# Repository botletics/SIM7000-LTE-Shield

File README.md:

## Overview
This shield uses SIMCOM's SIM7000-series module, a low-power cellular module that supports LTE CAT-M1 and NB-IoT technology and integrated multi-GNSS (GPS, GLONASS and BeiDou/Compass, Galileo, QZSS standards) for location tracking. The shield also includes a high-accuracy I2C temperature sensor for IoT monitoring applications.

- [Buy shield on Amazon](http://a.co/d/eQ2l2TL)
- [Step-by-step wiki](https://github.com/botletics/SIM7000-LTE-Shield/wiki)
- [Arduino library with example code](https://github.com/botletics/Botletics-SIM7000) 
- [Botletics community forum](https://forum.botletics.com/) 

All PCB design files and hardware are released under the [Creative Commons Attribution Share Alike 4.0 license](https://choosealicense.com/licenses/cc-by-sa-4.0/).

All other software is released under the [GNU General Public License v3.0](https://choosealicense.com/licenses/gpl-3.0/).

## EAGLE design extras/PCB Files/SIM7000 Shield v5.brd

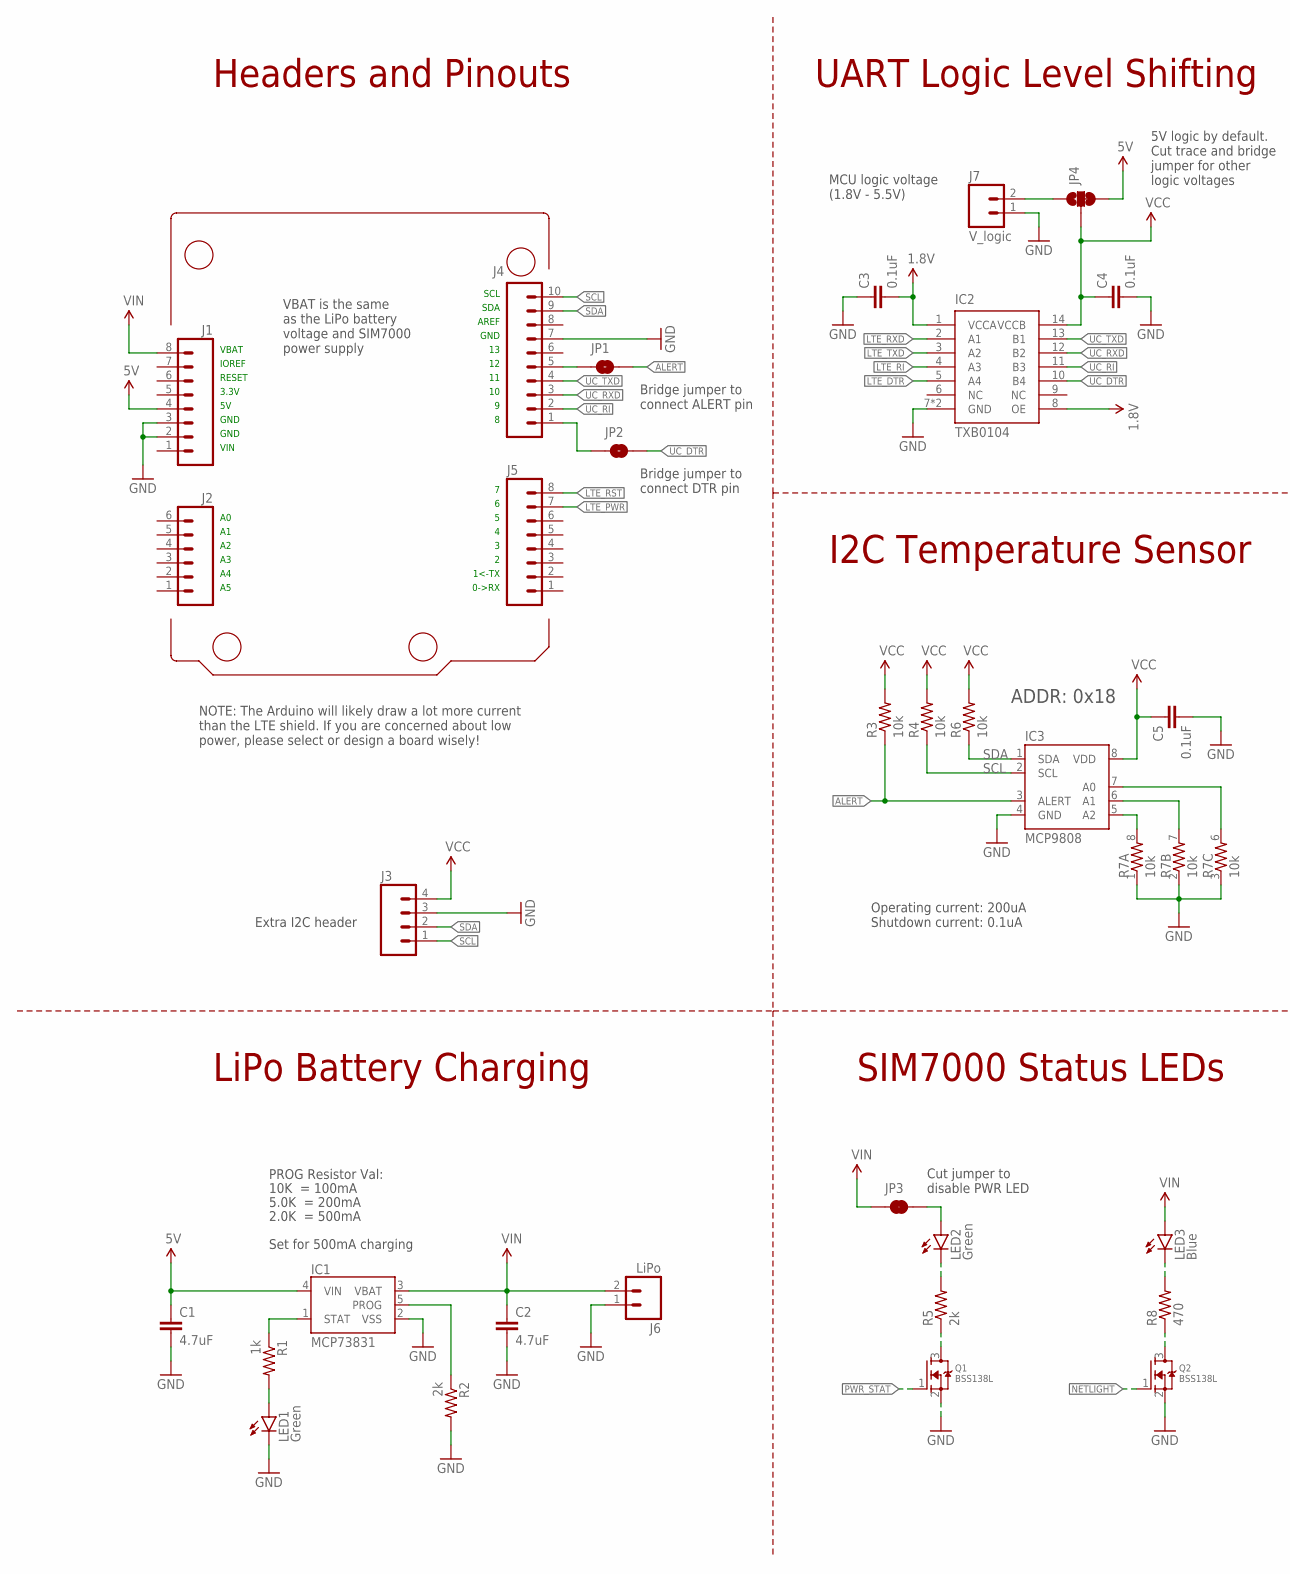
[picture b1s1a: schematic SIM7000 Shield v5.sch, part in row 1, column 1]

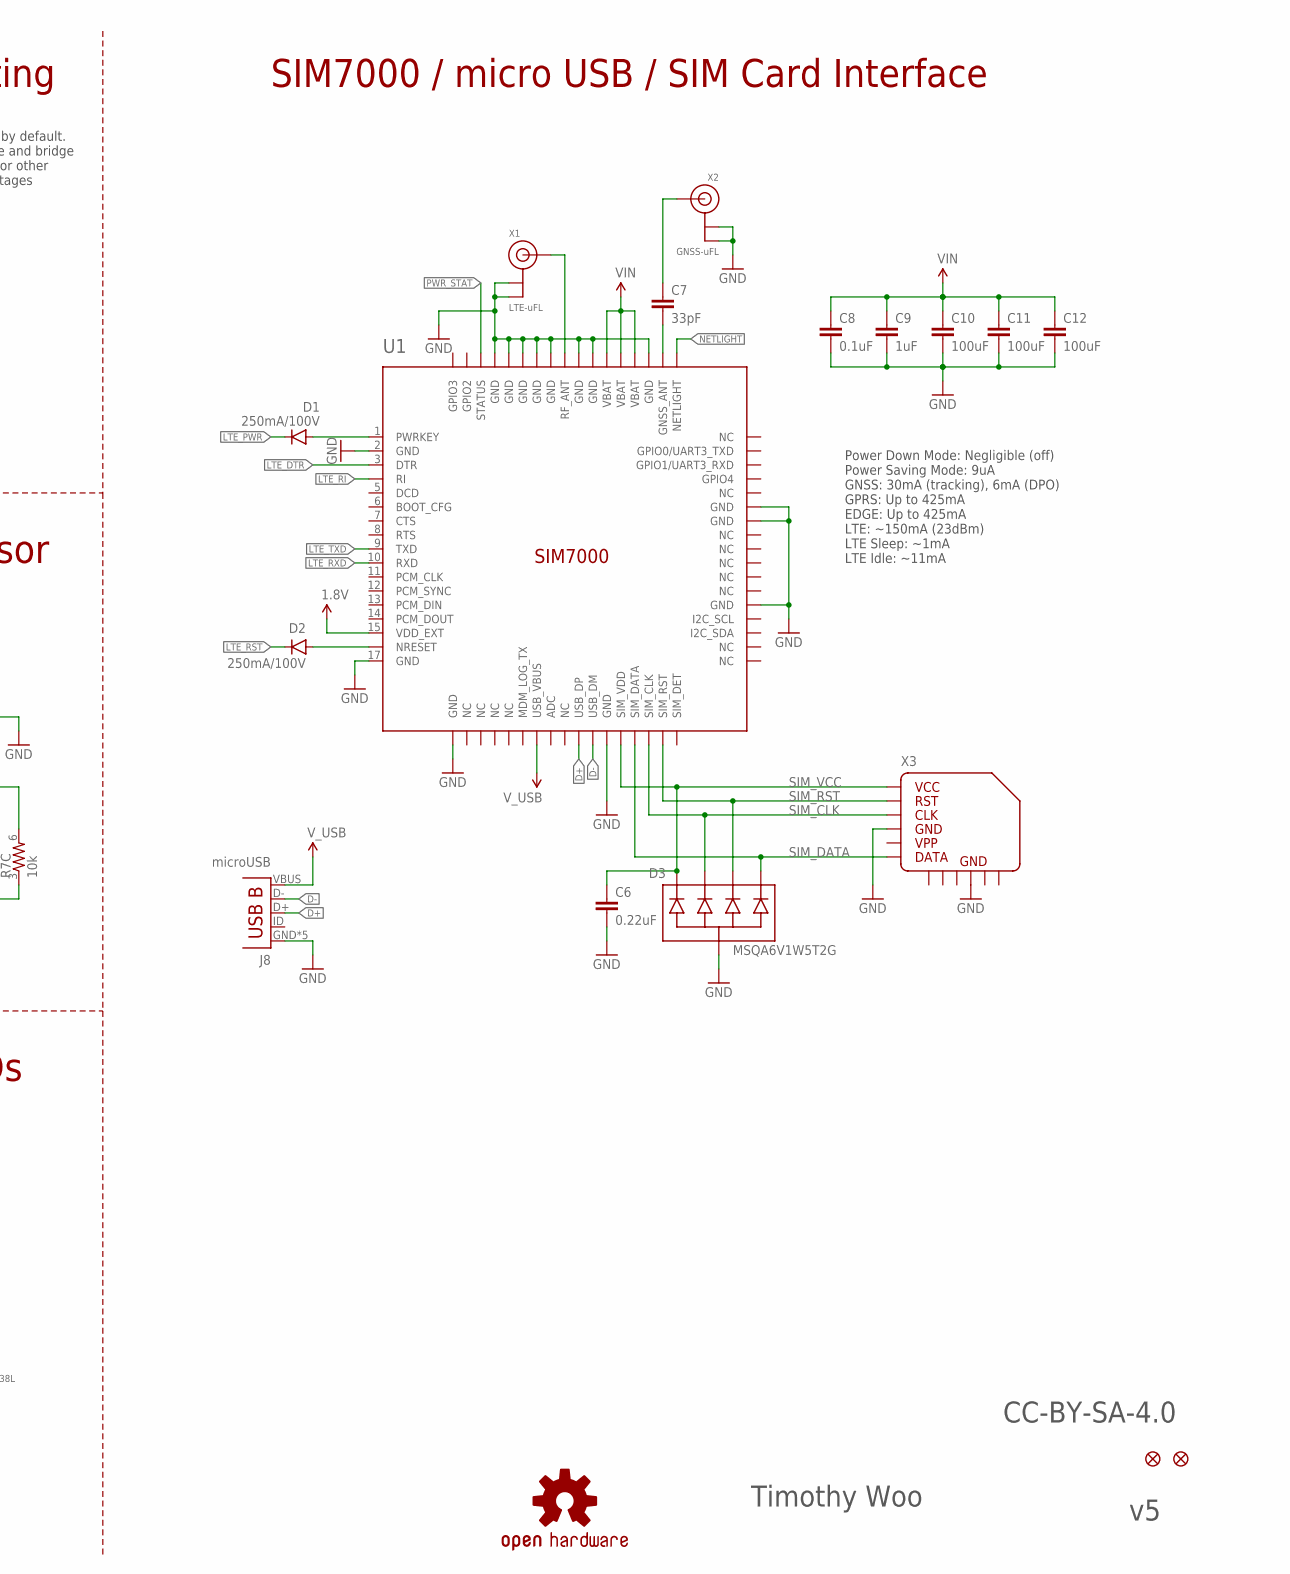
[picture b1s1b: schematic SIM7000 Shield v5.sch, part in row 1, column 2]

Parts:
C1, C2: 4.7uF; 0603-CAP-MARKED
C3, C4, C5, C8: 0.1uF; 0603-CAP-MARKED
C6: 0.22uF; 0603-CAP-MARKED
C7: 33pF; 0603-CAP-MARKED
C9: 1uF; 0603-CAP-MARKED
C10, C11, C12: 100uF; 1210
D1, D2: 250mA/100V; SOD-323
D3: MSQA6V1W5T2G; SOT-353
FID1, FID2: FIDUCIAL; FIDUCIAL_1MM
IC1: MCP73831; SOT23-5
IC2: TXB0104; VQFN-14
IC3: MCP9808; 8-TSSOP
J1, J5: M08SILK_PTH; 1X08
J2: M06SILK_PTH; 1X06
J3: M04PTH-ROUND; 1X04_ROUND
J4: M10SILK_PTH; 1X10
J6: LiPo; JST-2-SMD
J7: V_logic; 1X02
J8: microUSB; USB-B-MICRO-SMD
JP1, JP2: JUMPER-SMT_2_NO_SILK; SMT-JUMPER_2_NO_SILK
JP3: JUMPER-SMT_2_NC_TRACE_SILK; SMT-JUMPER_2_NC_TRACE_SILK
JP4: JUMPER-SMT_3_1-NC_TRACE_SILK; SMT-JUMPER_3_1-NC_TRACE_SILK
LED1, LED2: Green; LED-0603-MARKED
LED3: Blue; LED-0603-MARKED
LOGO1: OSHW-LOGOL; OSHW-LOGO-L
Q1, Q2: BSS138L; SOT23-3
R1: 1k; 0603-RES-MARKED
R2, R5: 2k; 0603-RES-MARKED
R3, R4, R6: 10k; 0603-RES-MARKED
R7: 10k; RES_ARRAY_4X0603
R8: 470; 0603-RES-MARKED
U1: SIM7000
X1: LTE-uFL; U.FL
X2: GNSS-uFL; U.FL
X3: MICROSIM_SOCKET_PUSH-PULL

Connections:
1.8V: C3.2, IC2.1 (VCCA), IC2.8 (OE), U1.15 (VDD_EXT)
5V: C1.1, IC1.4 (VIN), J1.4, JP4.3
ADDR0: IC3.7 (A0), R7.6 (2)
ADDR1: IC3.6 (A1), R7.7 (2)
ADDR2: IC3.5 (A2), R7.8 (2)
ALERT: IC3.3 (ALERT), JP1.2, R3.1
D+: J8.D+, U1.27 (USB_DP)
D-: J8.D-, U1.28 (USB_DM)
GND: C1.2, C2.2, C3.1, C4.2, C5.2, C6.2, C8.2, C9.2, C10.2, C11.2, C12.2, D3.2 (COM), IC1.2 (VSS), IC2.7 (GND), IC2.PAD (GND), IC3.4 (GND), J1.2, J1.3, J3.3, J4.7, J6.1 (2), J7.1, J8.GND, J8.SHIELD1 (GND), J8.SHIELD2 (GND), J8.SHIELD3 (GND), J8.SHIELD4 (GND), LED1.C, Q1.2 (S), Q2.2 (S), R2.2, R7.1, R7.2 (1), R7.3 (1), U1.2 (GND), U1.17 (GND), U1.18 (GND), U1.29 (GND), U1.39 (GND), U1.45 (GND), U1.46 (GND), U1.54 (GND), U1.58 (GND), U1.59 (GND), U1.61 (GND), U1.62 (GND), U1.63 (GND), U1.64 (GND), U1.65 (GND), X1.1 (GND), X1.2 (GND), X2.1 (GND), X2.2 (GND), X3.C5, X3.GND@1 (GND), X3.GND@2 (GND), X3.GND@3 (GND), X3.GND@4 (GND), X3.GND@5 (GND), X3.GND@6 (GND)
LTE_DTR: IC2.5 (A4), U1.3 (DTR)
LTE_PWR: D1.C, J5.7
LTE_RI: IC2.4 (A3), U1.4 (RI)
LTE_RST: D2.C, J5.8
LTE_RXD: IC2.2 (A1), U1.10 (RXD)
LTE_TXD: IC2.3 (A2), U1.9 (TXD)
unnamed: C7.2, U1.53 (GNSS_ANT)
unnamed: D1.A, U1.1 (PWRKEY)
unnamed: C7.1, X2.3 (SIGNAL)
unnamed: Q1.3 (D), R5.1
unnamed: LED2.C, R5.2
unnamed: J4.5, JP1.1
unnamed: J4.1, JP2.1
unnamed: Q2.3 (D), R8.1
unnamed: LED3.C, R8.2
unnamed: JP3.2, LED2.A
unnamed: LED1.A, R1.2
NETLIGHT: Q2.1 (G), U1.52 (NETLIGHT)
NRESET: D2.A, U1.16 (NRESET)
PROG: IC1.5 (PROG), R2.1
PWR_STAT: Q1.1 (G), U1.66 (STATUS)
RF_ANT: U1.60 (RF_ANT), X1.3 (SIGNAL)
SCL: IC3.2 (SCL), J3.1, J4.10, R4.1
SDA: IC3.1 (SDA), J3.2, J4.9, R6.1
SIM_CLK: D3.3 (2), U1.32 (SIM_CLK), X3.C3
SIM_DATA: D3.5 (4), U1.31 (SIM_DATA), X3.C7
SIM_RST: D3.4 (3), U1.33 (SIM_RST), X3.C2
SIM_VCC: C6.1, D3.1, U1.30 (SIM_VDD), X3.C1
STAT: IC1.1 (STAT), R1.1
UC_DTR: IC2.10 (B4), JP2.2
UC_RI: IC2.11 (B3), J4.2
UC_RXD: IC2.12 (B2), J4.3
UC_TXD: IC2.13 (B1), J4.4
VCC: C4.1, C5.1, IC2.14 (VCCB), IC3.8 (VDD), J3.4, JP4.2, R3.2, R4.2, R6.2
VIN: C2.1, C8.1, C9.1, C10.1, C11.1, C12.1, IC1.3 (VBAT), J1.8, J6.2 (1), JP3.1, LED3.A, U1.55 (VBAT), U1.56 (VBAT), U1.57 (VBAT)
V_LOGIC: J7.2, JP4.1
V_USB: J8.VBUS, U1.24 (USB_VBUS)

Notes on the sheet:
IOREF
3.3V
RESET
GND
VIN
0->RX
1<-TX
AREF
SDA
SCL
Timothy Woo
CC-BY-SA-4.0
SIM7000 / micro USB / SIM Card Interface
Headers and Pinouts
LiPo Battery Charging
I2C Temperature Sensor
ADDR: 0x18
UART Logic Level Shifting
VBAT
SIM7000 Status LEDs
Cut jumper to disable PWR LED
Power Down Mode: Negligible (off) Power Saving Mode: 9uA GNSS: 30mA (tracking), 6mA (DPO) GPRS: Up to 425mA EDGE: Up to 425mA LTE: ~150mA (23dBm) LTE Sleep: ~1mA LTE Idle: ~11mA
NOTE: The Arduino will likely draw a lot more current than the LTE shield. If you are concerned about low power, please select or design a board wisely!
Extra I2C header
Bridge jumper to connect DTR pin
Bridge jumper to connect ALERT pin
Operating current: 200uA Shutdown current: 0.1uA
MCU logic voltage (1.8V - 5.5V)
5V logic by default. Cut trace and bridge jumper for other logic voltages
Set for 500mA charging
10K = 100mA
5.0K = 200mA
2.0K = 500mA
PROG Resistor Val:
VBAT is the same as the LiPo battery voltage and SIM7000 power supply

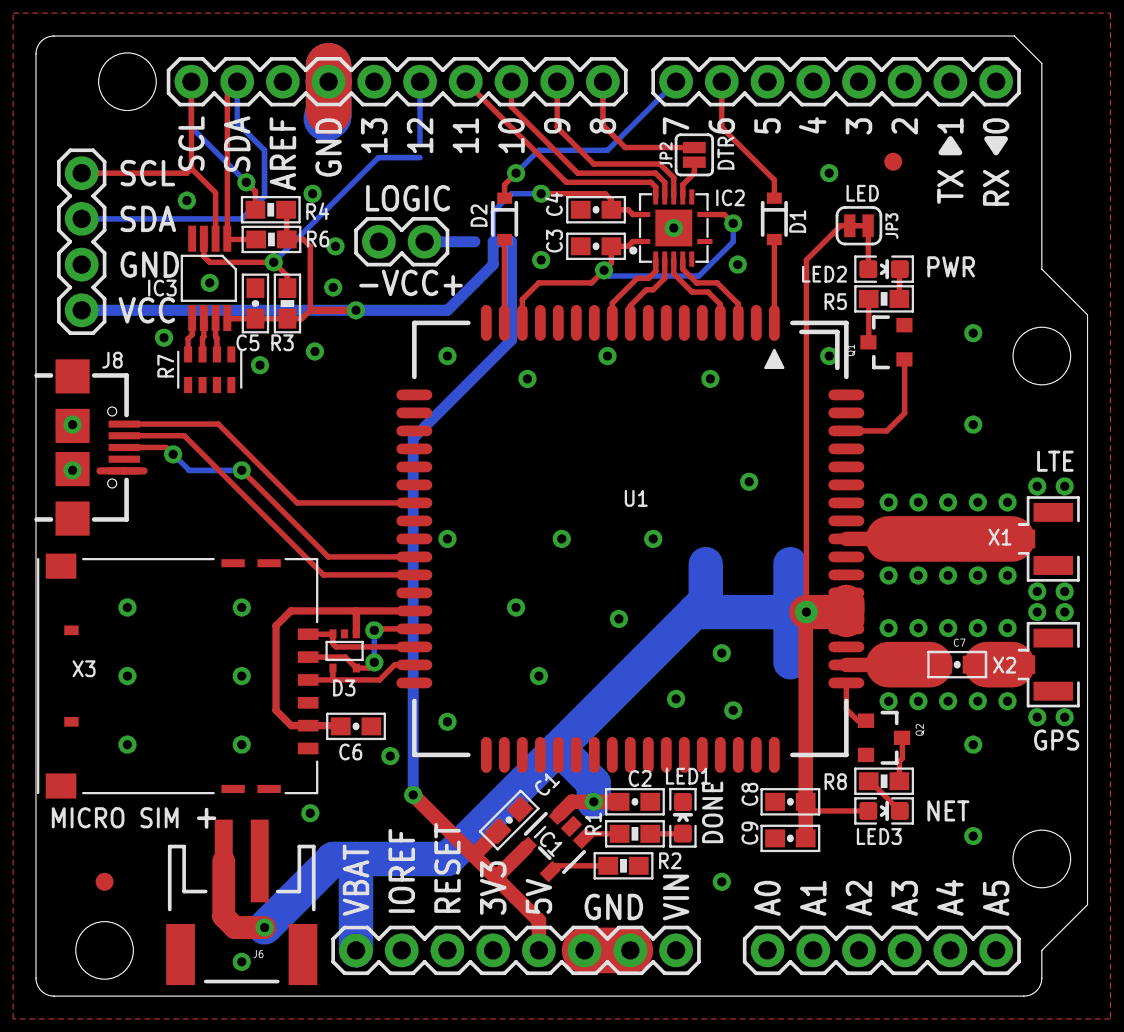
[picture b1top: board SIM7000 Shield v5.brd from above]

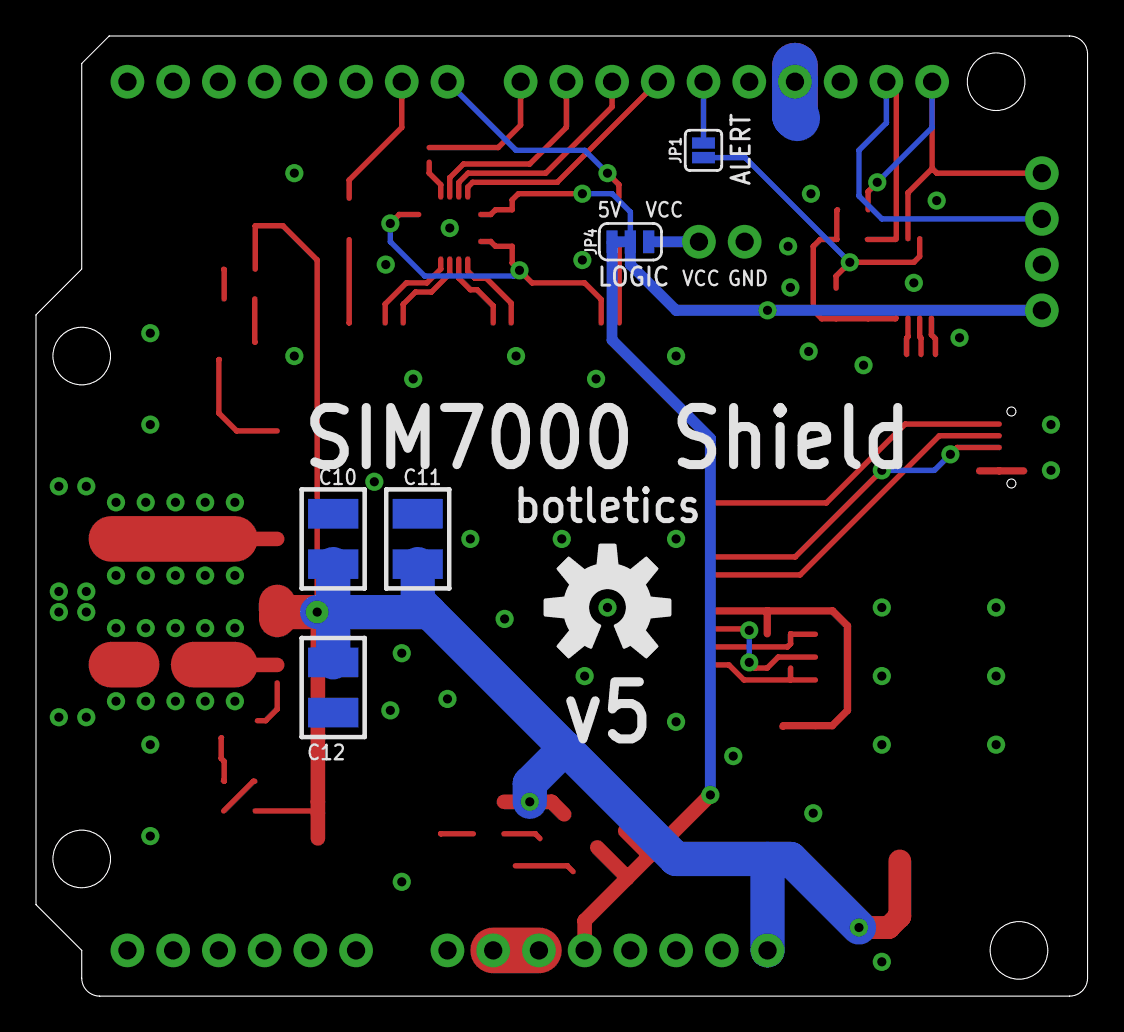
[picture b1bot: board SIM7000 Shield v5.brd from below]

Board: 2 copper layers, 58.4 x 53.3 mm, 50 parts (6 on the bottom side), 46 nets.

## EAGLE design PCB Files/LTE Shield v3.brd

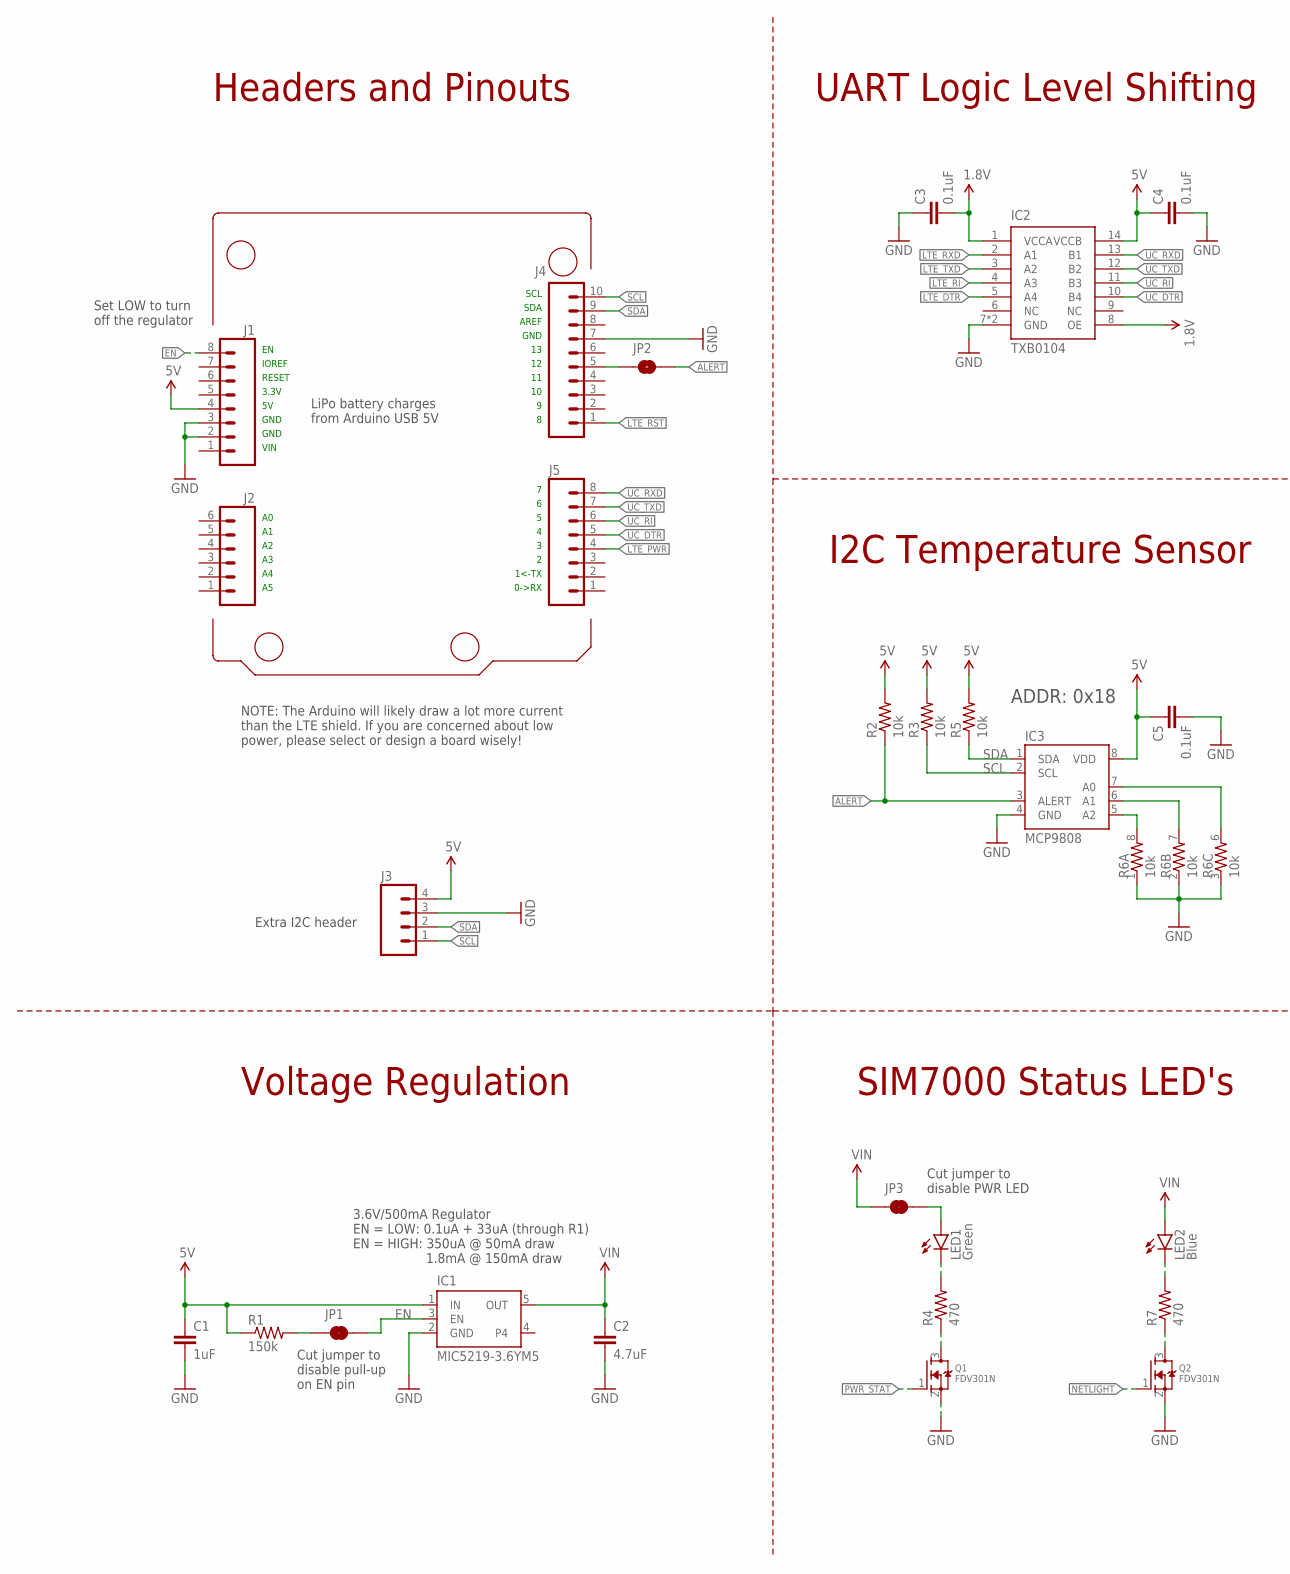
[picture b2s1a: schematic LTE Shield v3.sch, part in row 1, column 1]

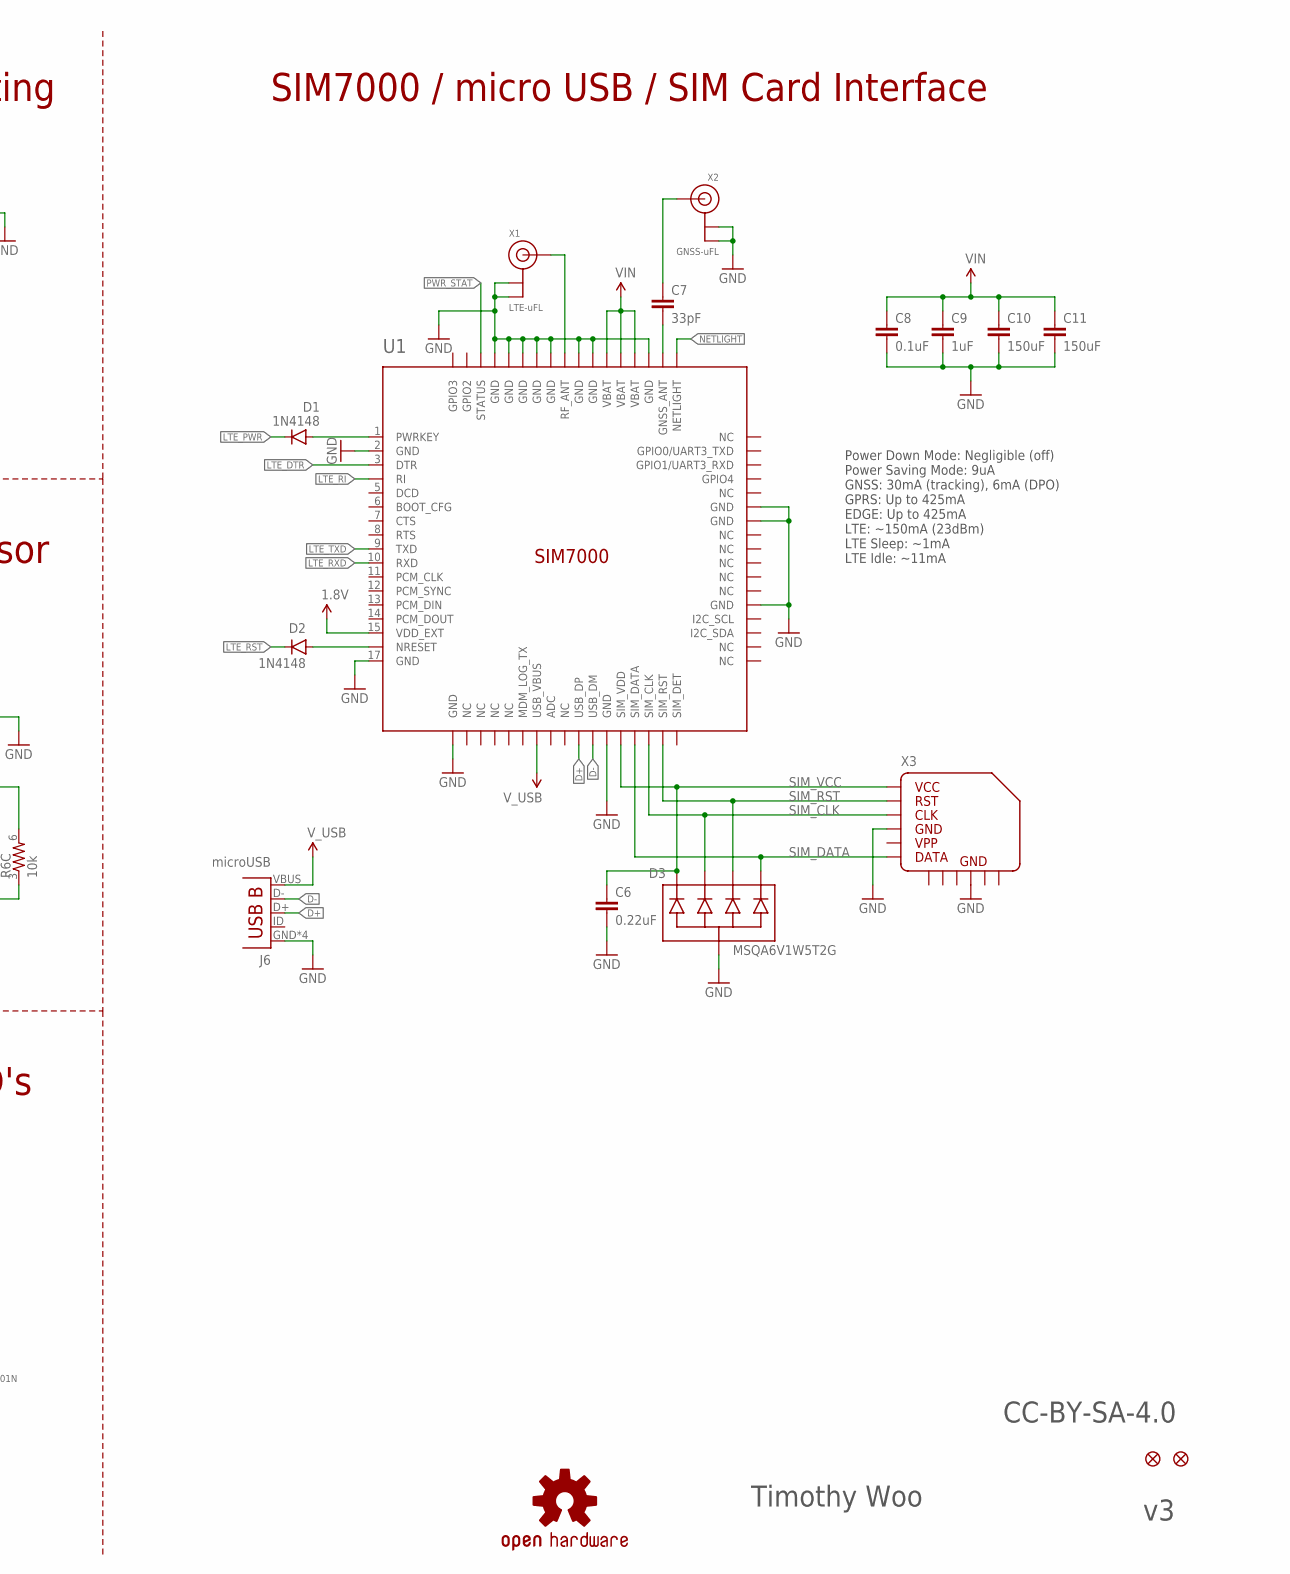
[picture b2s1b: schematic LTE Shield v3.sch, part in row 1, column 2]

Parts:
C1, C9: 1uF; 0603-CAP-MARKED
C2: 4.7uF; 0603-CAP-MARKED
C3, C4, C5, C8: 0.1uF; 0603-CAP-MARKED
C6: 0.22uF; 0603-CAP-MARKED
C7: 33pF; 0603-CAP-MARKED
C10, C11: 150uF; 1206
D1, D2: 1N4148; SOD-323
D3: MSQA6V1W5T2G; SOT-353
FID1, FID2: FIDUCIAL; FIDUCIAL_1MM
IC1: MIC5219-3.6YM5; SOT23-5
IC2: TXB0104; VQFN-14
IC3: MCP9808; 8-TSSOP
J1, J5: M08SILK_PTH; 1X08
J2: M06SILK_PTH; 1X06
J3: M04PTH-ROUND; 1X04_ROUND
J4: M10SILK_PTH; 1X10
J6: microUSB; USB-B-MICRO-SMD
JP1, JP3: JUMPER-SMT_2_NC_TRACE_SILK; SMT-JUMPER_2_NC_TRACE_SILK
JP2: JUMPER-SMT_2_NO_SILK; SMT-JUMPER_2_NO_SILK
LED1: Green; LED-0603-MARKED
LED2: Blue; LED-0603-MARKED
LOGO1: OSHW-LOGOL; OSHW-LOGO-L
Q1, Q2: FDV301N; SOT23-3
R1: 150k; 0603-RES-MARKED
R2, R3, R5: 10k; 0603-RES-MARKED
R4, R7: 470; 0603-RES-MARKED
R6: 10k; RES_ARRAY_4X0603
U1: SIM7000
X1: LTE-uFL; U.FL
X2: GNSS-uFL; U.FL
X3: MICROSIM_SOCKET_PUSH-PULL

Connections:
1.8V: C3.2, IC2.1 (VCCA), IC2.8 (OE), U1.15 (VDD_EXT)
5V: C1.1, C4.1, C5.1, IC1.1 (IN), IC2.14 (VCCB), IC3.8 (VDD), J1.4, J3.4, R1.1, R2.2, R3.2, R5.2
ADDR0: IC3.7 (A0), R6.6 (2)
ADDR1: IC3.6 (A1), R6.7 (2)
ADDR2: IC3.5 (A2), R6.8 (2)
ALERT: IC3.3 (ALERT), JP2.2, R2.1
D+: J6.D+, U1.27 (USB_DP)
D-: J6.D-, U1.28 (USB_DM)
EN: IC1.3 (EN), J1.8, JP1.2
GND: C1.2, C2.2, C3.1, C4.2, C5.2, C6.2, C8.2, C9.2, C10.2, C11.2, D3.2 (COM), IC1.2 (GND), IC2.7 (GND), IC2.PAD (GND), IC3.4 (GND), J1.2, J1.3, J3.3, J4.7, J6.GND, J6.SHIELD1 (GND), J6.SHIELD2 (GND), J6.SHIELD3 (GND), Q1.2 (S), Q2.2 (S), R6.1, R6.2 (1), R6.3 (1), U1.2 (GND), U1.17 (GND), U1.18 (GND), U1.29 (GND), U1.39 (GND), U1.45 (GND), U1.46 (GND), U1.54 (GND), U1.58 (GND), U1.59 (GND), U1.61 (GND), U1.62 (GND), U1.63 (GND), U1.64 (GND), U1.65 (GND), X1.1 (GND), X1.2 (GND), X2.1 (GND), X2.2 (GND), X3.C5, X3.GND@1 (GND), X3.GND@2 (GND), X3.GND@3 (GND), X3.GND@4 (GND), X3.GND@5 (GND), X3.GND@6 (GND)
LTE_DTR: IC2.5 (A4), U1.3 (DTR)
LTE_PWR: D1.C, J5.4
LTE_RI: IC2.4 (A3), U1.4 (RI)
LTE_RST: D2.C, J4.1
LTE_RXD: IC2.2 (A1), U1.10 (RXD)
LTE_TXD: IC2.3 (A2), U1.9 (TXD)
unnamed: C7.2, U1.53 (GNSS_ANT)
unnamed: D1.A, U1.1 (PWRKEY)
unnamed: C7.1, X2.3 (SIGNAL)
unnamed: Q1.3 (D), R4.1
unnamed: LED1.C, R4.2
unnamed: JP1.1, R1.2
unnamed: J4.5, JP2.1
unnamed: Q2.3 (D), R7.1
unnamed: LED2.C, R7.2
unnamed: JP3.2, LED1.A
NETLIGHT: Q2.1 (G), U1.52 (NETLIGHT)
NRESET: D2.A, U1.16 (NRESET)
PWR_STAT: Q1.1 (G), U1.66 (STATUS)
RF_ANT: U1.60 (RF_ANT), X1.3 (SIGNAL)
SCL: IC3.2 (SCL), J3.1, J4.10, R3.1
SDA: IC3.1 (SDA), J3.2, J4.9, R5.1
SIM_CLK: D3.3 (2), U1.32 (SIM_CLK), X3.C3
SIM_DATA: D3.5 (4), U1.31 (SIM_DATA), X3.C7
SIM_RST: D3.4 (3), U1.33 (SIM_RST), X3.C2
SIM_VCC: C6.1, D3.1, U1.30 (SIM_VDD), X3.C1
UC_DTR: IC2.10 (B4), J5.5
UC_RI: IC2.11 (B3), J5.6
UC_RXD: IC2.13 (B1), J5.8
UC_TXD: IC2.12 (B2), J5.7
VIN: C2.1, C8.1, C9.1, C10.1, C11.1, IC1.5 (OUT), JP3.1, LED2.A, U1.55 (VBAT), U1.56 (VBAT), U1.57 (VBAT)
V_USB: J6.VBUS, U1.24 (USB_VBUS)

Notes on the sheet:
IOREF
3.3V
RESET
GND
VIN
0->RX
1<-TX
AREF
SDA
SCL
LiPo battery charges from Arduino USB 5V
Timothy Woo
CC-BY-SA-4.0
SIM7000 / micro USB / SIM Card Interface
Headers and Pinouts
Voltage Regulation
I2C Temperature Sensor
ADDR: 0x18
UART Logic Level Shifting
Set LOW to turn off the regulator
SIM7000 Status LED's
Cut jumper to disable PWR LED
3.6V/500mA Regulator EN = LOW: 0.1uA + 33uA (through R1) EN = HIGH: 350uA @ 50mA draw 1.8mA @ 150mA draw
Power Down Mode: Negligible (off) Power Saving Mode: 9uA GNSS: 30mA (tracking), 6mA (DPO) GPRS: Up to 425mA EDGE: Up to 425mA LTE: ~150mA (23dBm) LTE Sleep: ~1mA LTE Idle: ~11mA
NOTE: The Arduino will likely draw a lot more current than the LTE shield. If you are concerned about low power, please select or design a board wisely!
Cut jumper to disable pull-up on EN pin
Extra I2C header

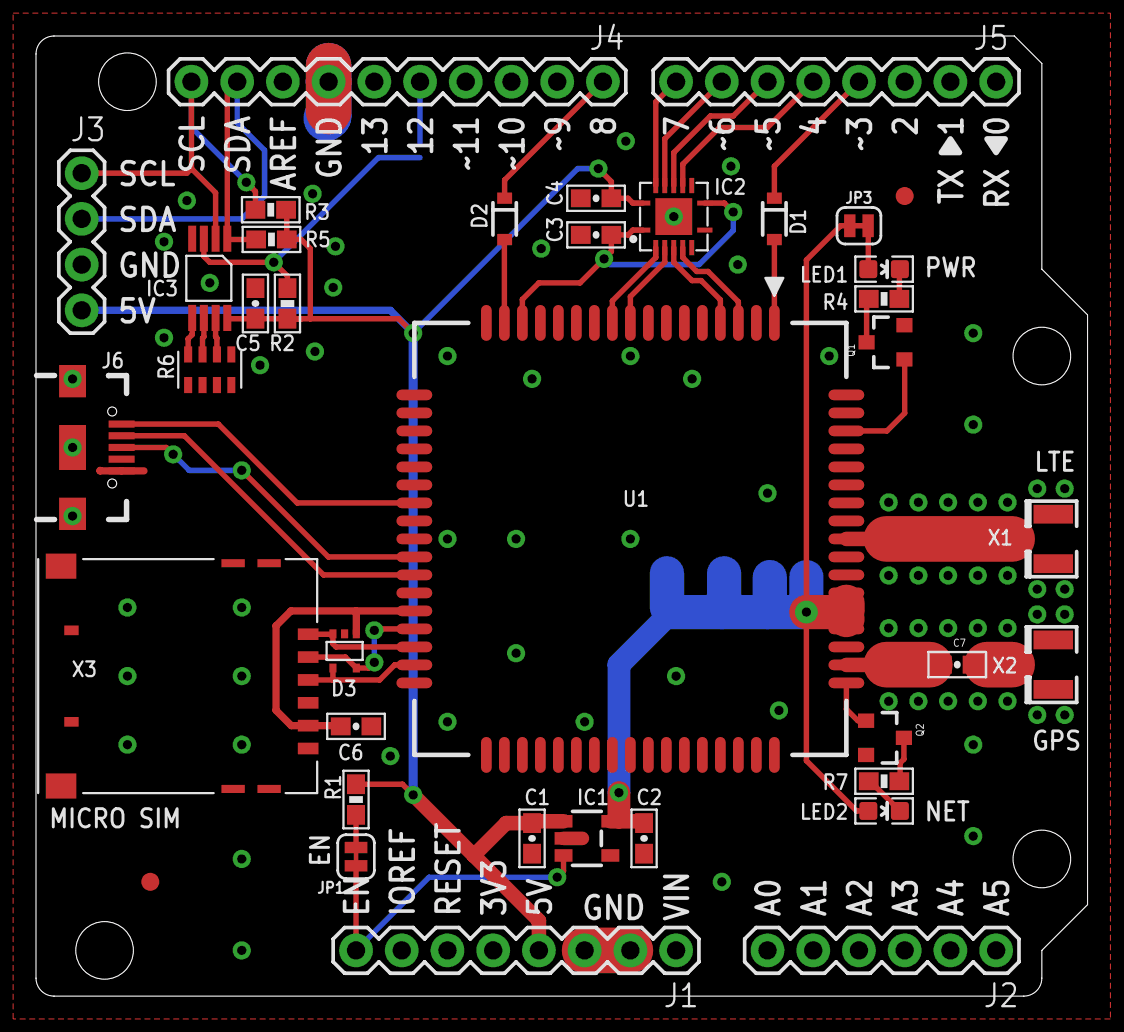
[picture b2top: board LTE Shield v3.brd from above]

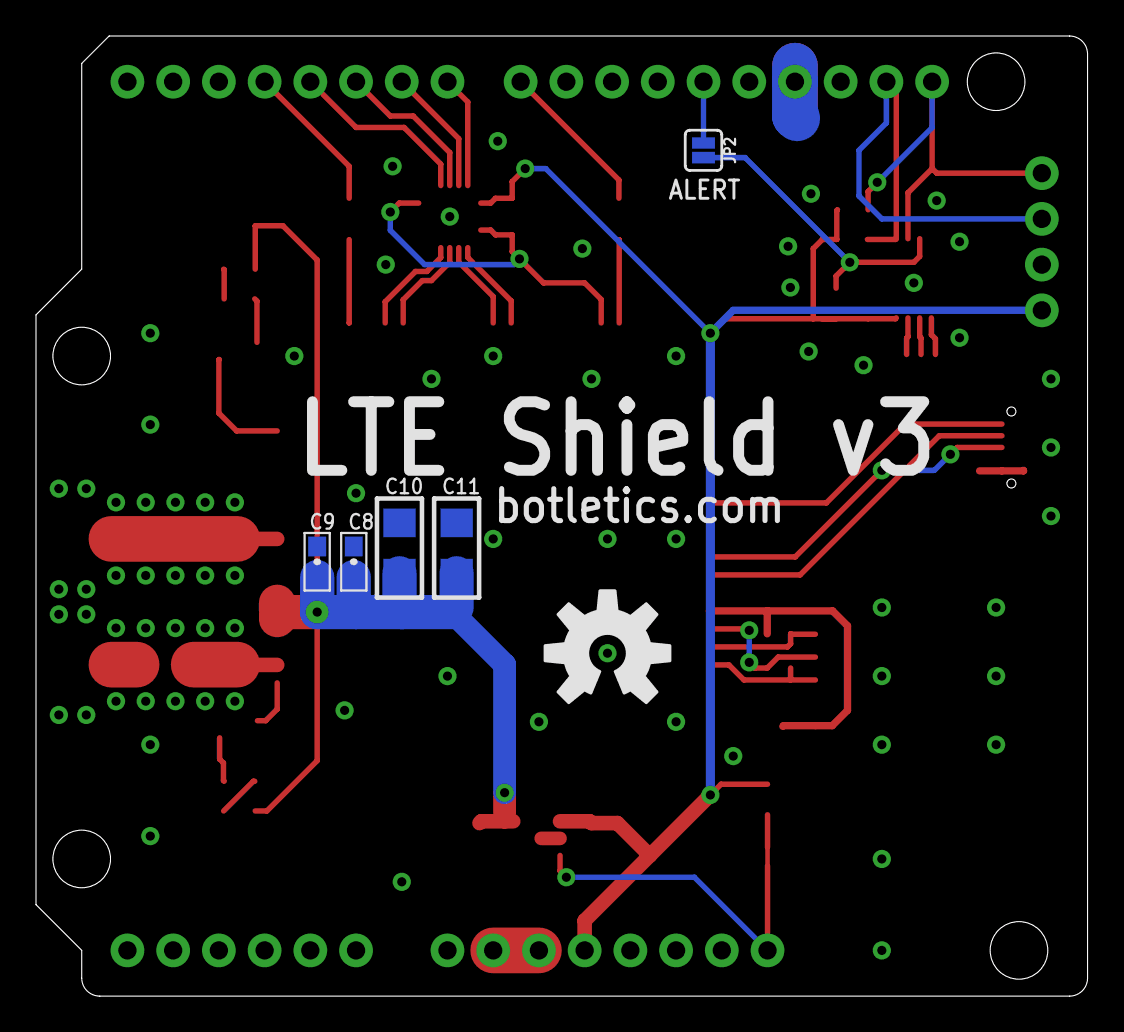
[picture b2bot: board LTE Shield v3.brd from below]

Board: 2 copper layers, 58.4 x 53.3 mm, 44 parts (6 on the bottom side), 42 nets.

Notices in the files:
PCB Files/LTE Shield v1.brd:
Released under CC-BY-SA-4.0 license
parts and their libraries:
SparkFun-Aesthetics: Licensing: Creative Commons ShareAlike 4.0 International - https://creativecommons.org/licenses/by-sa/4.0
